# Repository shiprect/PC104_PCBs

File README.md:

# PC104_PCBs
This repository contains a collection of PC104 form factor PCB designs used on a variety of projects.

__Branches__

_previous-revision_  :  for the previous iteration of the pcb that was manufactured

_current-revision_   :  the pcb files that we are currently updating/working on

_production_         : for the version we have currently ordered/produced/are testing

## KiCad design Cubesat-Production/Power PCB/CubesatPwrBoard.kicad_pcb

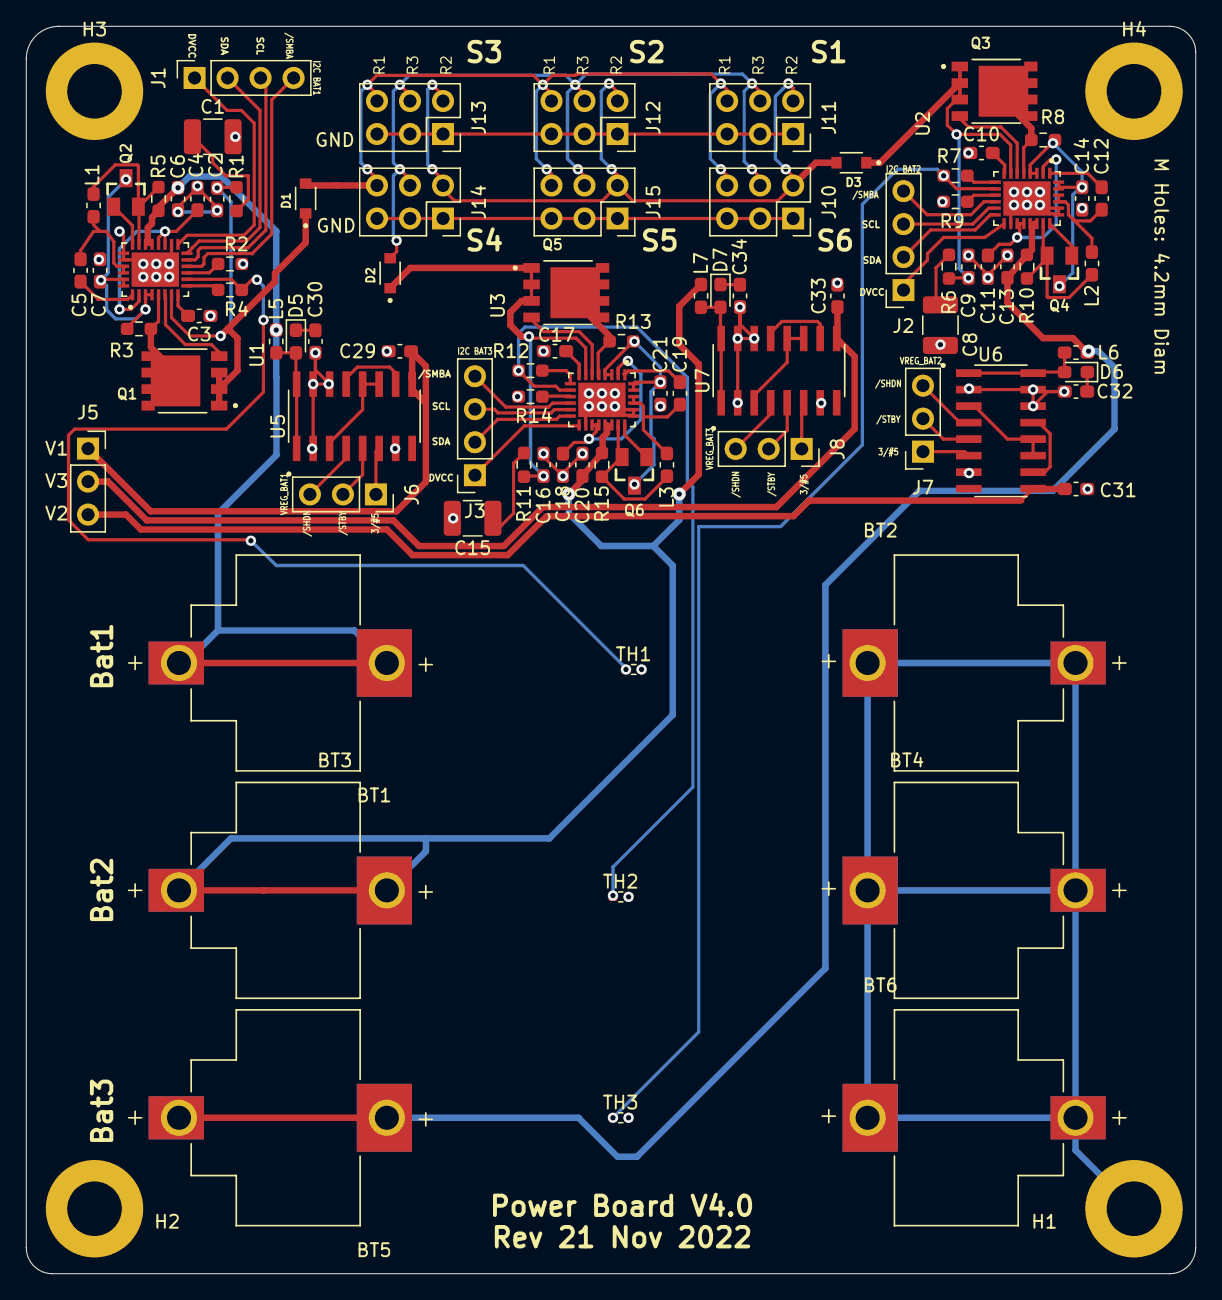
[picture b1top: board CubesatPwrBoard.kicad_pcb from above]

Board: 2 copper layers, 90.0 x 96.0 mm, 92 parts (0 on the bottom side), 85 nets.

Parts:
BT1, BT2, BT3, BT4, BT5, BT6: 254TR; BAT_254TR
C1: C_Polarized_US; C_1210_3225Metric_Pad1.33x2.70mm_HandSolder
C2, C9, C16, C29, C30: C_Polarized_US; C_0603_1608Metric_Pad1.08x0.95mm_HandSolder
C3, C4, C5, C6, C7, C12, C19: C; C_0603_1608Metric_Pad1.08x0.95mm_HandSolder
C8, C15: 150u; C_1210_3225Metric_Pad1.33x2.70mm_HandSolder
C10, C17: 1u; C_0603_1608Metric_Pad1.08x0.95mm_HandSolder
C11, C18, C31, C33: 4.7u; C_0603_1608Metric_Pad1.08x0.95mm_HandSolder
C13, C14, C20, C21: 10u; C_0603_1608Metric_Pad1.08x0.95mm_HandSolder
C32, C34: 100u; C_0603_1608Metric_Pad1.08x0.95mm_HandSolder
D1, D2, D3: D_Schottky_Small; DIO_CUS520,H3F
D5, D6, D7: D_Schottky; D_0603_1608Metric_Pad1.05x0.95mm_HandSolder
H1, H2, H3, H4: MountingHole_Pad; MountingHole_4.3mm_M4_DIN965_Pad
J1, J2, J3: Conn_01x04_Female; PinSocket_1x04_P2.54mm_Vertical
J5: Conn_01x04_Female; PinSocket_1x03_P2.54mm_Vertical
J6, J7, J8: Conn_01x03_Female; PinSocket_1x03_P2.54mm_Vertical
J10: S1; PinSocket_2x03_P2.54mm_Vertical
J11: S2; PinSocket_2x03_P2.54mm_Vertical
J12: S3; PinSocket_2x03_P2.54mm_Vertical
J13: S4; PinSocket_2x03_P2.54mm_Vertical
J14: S5; PinSocket_2x03_P2.54mm_Vertical
J15: S6; PinSocket_2x03_P2.54mm_Vertical
L1, L5: L; L_0603_1608Metric_Pad1.05x0.95mm_HandSolder
L2, L3: 4.7u; L_0603_1608Metric_Pad1.05x0.95mm_HandSolder
L6, L7: 22u; L_0603_1608Metric_Pad1.05x0.95mm_HandSolder
Q1, Q3, Q5: TQM110NB04CR_RLG; TRANS_TQM110NB04CR_RLG
Q2, Q4, Q6: 2N7002*; SOT23
R1, R2, R3, R4, R5: R; R_0603_1608Metric_Pad0.98x0.95mm_HandSolder
R6, R11: 2.5; R_0603_1608Metric_Pad0.98x0.95mm_HandSolder
R7, R8, R12, R13: 16m; R_0603_1608Metric_Pad0.98x0.95mm_HandSolder
R9, R14: 63.4k; R_0603_1608Metric_Pad0.98x0.95mm_HandSolder
R10, R15: 10m; R_0603_1608Metric_Pad0.98x0.95mm_HandSolder
TH1, TH2, TH3: Thermistor_NTC; R_0402_1005Metric_Pad0.72x0.64mm_HandSolder
U1, U2, U3: LTC4162; QFN50P500X400X80-29N
U5, U6, U7: MAX710ESE+T; SOIC127P600X175-16N

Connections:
/Bat_Reg_1/DVCC: J1.1, U1.15 (DVCC)
/Bat_Reg_1/SCL: J1.3, U1.13 (SCL)
/Bat_Reg_1/SDA: J1.2, U1.14 (SDA)
/Bat_Reg_1/TH: R2.2, TH1.1, U1.10 (NTC)
/Bat_Reg_1/VIN: C2.1, D1.1 (K), Q1.1, Q1.2, Q1.3, R1.1, U1.7 (VIN)
/Bat_Reg_1/V_Bat: BT1.P1_1, BT1.P1_2, C6.1, L5.1, R5.1, U1.19 (BATSENS+), U1.20 (CSN)
/Bat_Reg_1//SMBALERT: J1.4, U1.12 (/SMBALERT)
/Bat_Reg_2/DVCC: J3.1, U3.15 (DVCC)
/Bat_Reg_2/SCL: J3.3, U3.13 (SCL)
/Bat_Reg_2/SDA: J3.2, U3.14 (SDA)
/Bat_Reg_2/TH: R12.2, TH2.1, U3.10 (NTC)
/Bat_Reg_2/VIN: C16.1, D2.1 (K), Q5.1, Q5.2, Q5.3, R11.1, U3.7 (VIN)
/Bat_Reg_2/V_Bat: BT3.P1_1, BT3.P1_2, C20.1, L7.1, R15.1, U3.19 (BATSENS+), U3.20 (CSN)
/Bat_Reg_2//SMBALERT: J3.4, U3.12 (/SMBALERT)
/Bat_Reg_3/DVCC: J2.1, U2.15 (DVCC)
/Bat_Reg_3/SCL: J2.3, U2.13 (SCL)
/Bat_Reg_3/SDA: J2.2, U2.14 (SDA)
/Bat_Reg_3/TH: R7.2, TH3.1, U2.10 (NTC)
/Bat_Reg_3/VIN: C9.1, D3.1 (K), Q3.1, Q3.2, Q3.3, R6.1, U2.7 (VIN)
/Bat_Reg_3/V_Bat: BT5.P1_1, BT5.P1_2, C13.1, L6.1, R10.1, U2.19 (BATSENS+), U2.20 (CSN)
/Bat_Reg_3//SMBALERT: J2.4, U2.12 (/SMBALERT)
/V_Reg_3.3_5V1/3/#5: J6.1, U5.6 (3/~5)
/V_Reg_3.3_5V1/#SHDN: J6.3, U5.4 (~SHDN)
/V_Reg_3.3_5V1/#STBY: J6.2, U5.5 (~STBY)
/V_Reg_3.3_5V1/Vout: C29.1, J5.1, U5.9 (OUT)
/V_Reg_3.3_5V2/3/#5: J8.1, U7.6 (3/~5)
/V_Reg_3.3_5V2/#SHDN: J8.3, U7.4 (~SHDN)
/V_Reg_3.3_5V2/#STBY: J8.2, U7.5 (~STBY)
/V_Reg_3.3_5V2/Vout: C33.1, J5.2, U7.9 (OUT)
/V_Reg_3.3_5V3/3/#5: J7.1, U6.6 (3/~5)
/V_Reg_3.3_5V3/#SHDN: J7.3, U6.4 (~SHDN)
/V_Reg_3.3_5V3/#STBY: J7.2, U6.5 (~STBY)
/V_Reg_3.3_5V3/Vout: C31.1, J5.3, U6.9 (OUT)
GND: BT2.P1_1, BT2.P1_2, BT4.P1_1, BT4.P1_2, BT6.P1_1, BT6.P1_2, C1.2, C2.2, C3.1, C4.2, C6.2, C7.2, C8.2, C9.2, C10.1, C11.2, C13.2, C14.2, C15.2, C16.2, C17.1, C18.2, C20.2, C21.2, C29.2, C30.2, C31.2, C32.2, C33.2, C34.2, H1.1, H2.1, H3.1, H4.1, J10.1, J10.3, J10.5, J11.1, J11.3, J11.5, J12.1, J12.3, J12.5, J13.1, J13.3, J13.5, J14.1, J14.3, J14.5, J15.1, J15.3, J15.5, R4.1, R9.1, R14.1, TH1.2, TH2.2, TH3.2, U1.16 (SYNC), U1.23 (PGND), U1.24 (PGND), U1.29 (AGND), U2.16 (SYNC), U2.23 (PGND), U2.24 (PGND), U2.29 (AGND), U3.16 (SYNC), U3.23 (PGND), U3.24 (PGND), U3.29 (AGND), U5.2 (PGND), U5.7 (N/~E), U5.14 (GND), U5.15 (PGND), U6.2 (PGND), U6.7 (N/~E), U6.14 (GND), U6.15 (PGND), U7.2 (PGND), U7.7 (N/~E), U7.14 (GND), U7.15 (PGND)
unnamed: C1.1, R1.2
unnamed: C3.2, U1.8 (VCC2P5)
unnamed: C4.1, U1.2 (INTVCC), U1.17 (CELLS0), U1.18 (CELLS1)
unnamed: C5.1, U1.1 (BOOST)
unnamed: C5.2, L1.1, U1.25 (SW), U1.26 (SW)
unnamed: C7.1, Q2.3, R3.1, U1.3 (VOUTA), U1.4 (CLN), U1.27 (VOUT), U1.28 (VOUT)
unnamed: C8.1, R6.2
unnamed: C10.2, U2.8 (VCC2P5)
unnamed: C11.1, U2.2 (INTVCC), U2.17 (CELLS0), U2.18 (CELLS1)
unnamed: C12.1, U2.1 (BOOST)
unnamed: C12.2, L2.1, U2.25 (SW), U2.26 (SW)
unnamed: C14.1, Q4.3, R8.1, U2.3 (VOUTA), U2.4 (CLN), U2.27 (VOUT), U2.28 (VOUT)
unnamed: C15.1, R11.2
unnamed: C17.2, U3.8 (VCC2P5)
unnamed: C18.1, U3.2 (INTVCC), U3.17 (CELLS0), U3.18 (CELLS1)
unnamed: C19.1, U3.1 (BOOST)
unnamed: C19.2, L3.1, U3.25 (SW), U3.26 (SW)
unnamed: C21.1, Q6.3, R13.1, U3.3 (VOUTA), U3.4 (CLN), U3.27 (VOUT), U3.28 (VOUT)
unnamed: C30.1, D5.1 (K)
unnamed: C32.1, D6.1 (K)
unnamed: C34.1, D7.1 (K)
unnamed: D1.2 (A), J10.6, J11.6, J12.6, J13.6, J14.6, J15.6
unnamed: D2.2 (A), J10.4, J11.4, J12.4, J13.4, J14.4, J15.4
unnamed: D3.2 (A), J10.2, J11.2, J12.2, J13.2, J14.2, J15.2
unnamed: D5.2 (A), L5.2, U5.1 (LX), U5.16 (LX)
unnamed: D6.2 (A), L6.2, U6.1 (LX), U6.16 (LX)
unnamed: D7.2 (A), L7.2, U7.1 (LX), U7.16 (LX)
unnamed: L1.2, Q2.2, R5.2, U1.21 (CSP)
unnamed: L2.2, Q4.2, R10.2, U2.21 (CSP)
unnamed: L3.2, Q6.2, R15.2, U3.21 (CSP)
unnamed: Q1.4, U1.6 (INFET)
unnamed: Q1.5_8, R3.2, U1.5 (CLP)
unnamed: Q2.1, U1.22 (BATFET)
unnamed: Q3.4, U2.6 (INFET)
unnamed: Q3.5_8, R8.2, U2.5 (CLP)
unnamed: Q4.1, U2.22 (BATFET)
unnamed: Q5.4, U3.6 (INFET)
unnamed: Q5.5_8, R13.2, U3.5 (CLP)
unnamed: Q6.1, U3.22 (BATFET)
unnamed: R2.1, U1.9 (NTCBIAS)
unnamed: R4.2, U1.11 (RT)
unnamed: R7.1, U2.9 (NTCBIAS)
unnamed: R9.2, U2.11 (RT)
unnamed: R12.1, U3.9 (NTCBIAS)
unnamed: R14.2, U3.11 (RT)
unnamed: U5.10 (LBI-), U5.13 (REF)
unnamed: U5.3 (ILIM), U5.11 (LBI+), U5.12 (PS)
unnamed: U6.10 (LBI-), U6.13 (REF)
unnamed: U6.3 (ILIM), U6.11 (LBI+), U6.12 (PS)
unnamed: U7.10 (LBI-), U7.13 (REF)
unnamed: U7.3 (ILIM), U7.11 (LBI+), U7.12 (PS)

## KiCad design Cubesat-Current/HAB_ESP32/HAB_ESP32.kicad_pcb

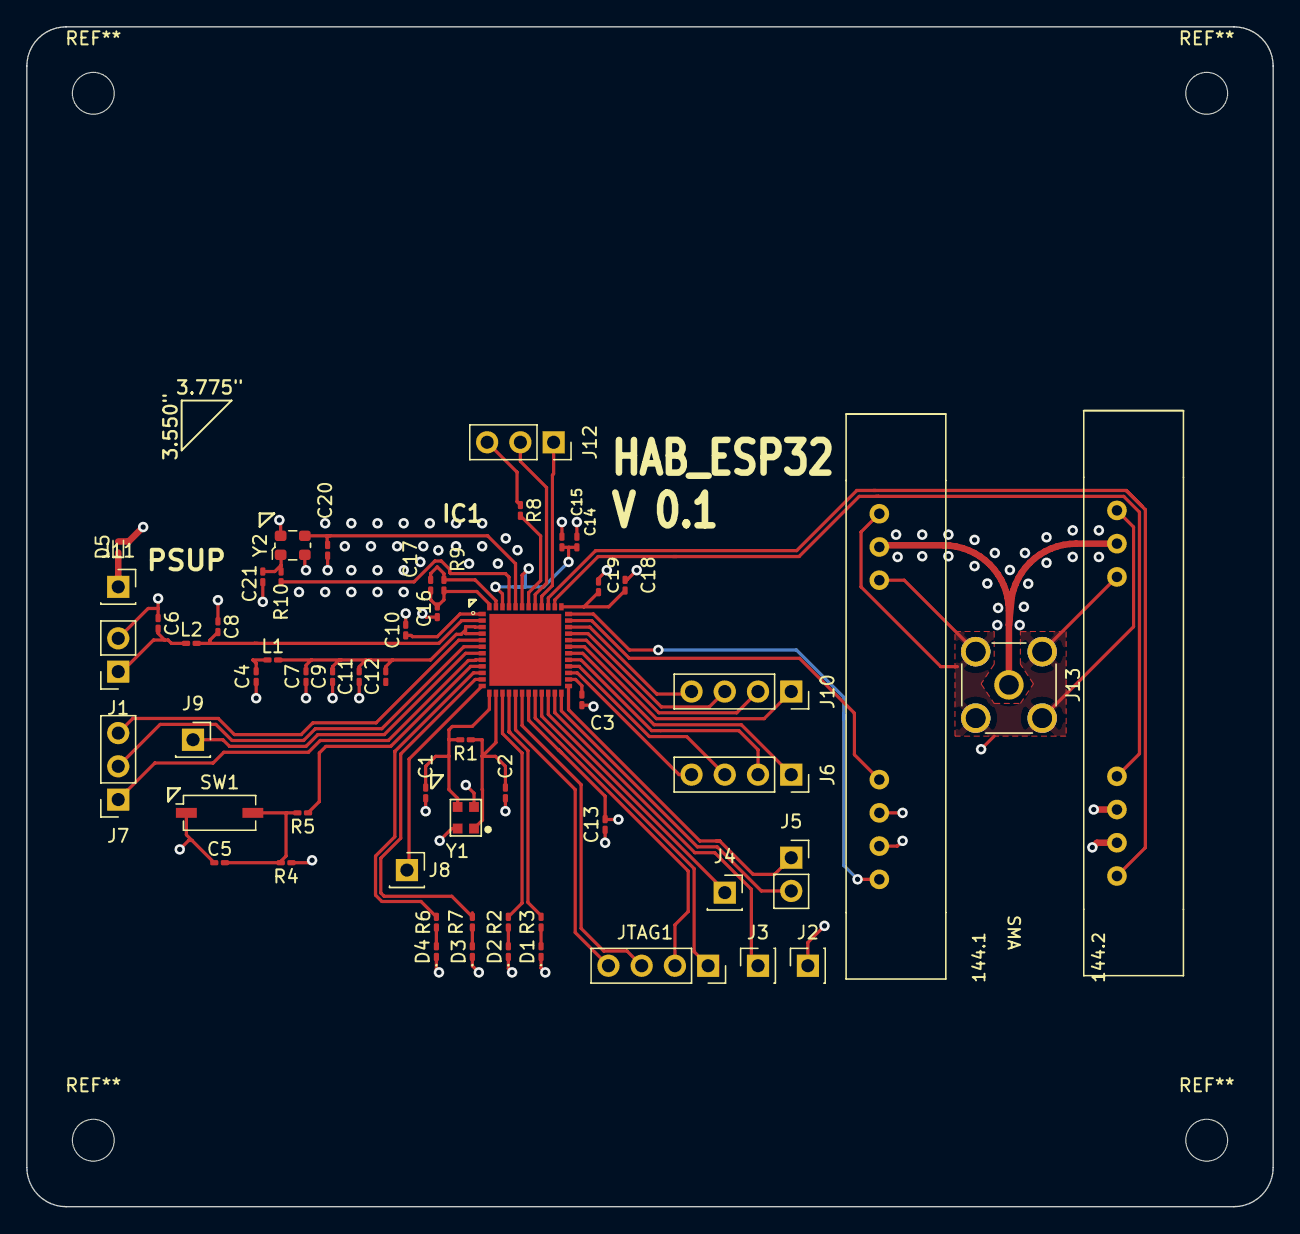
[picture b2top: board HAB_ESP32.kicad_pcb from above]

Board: 4 copper layers, 95.2 x 90.2 mm, 58 parts (0 on the bottom side), 54 nets.

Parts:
144.1, 144.2: Radiometic_HX1; Radiometric_HX1
C1, C2, C6, C8, C20: TBD; C_0201_0603Metric_Pad0.64x0.40mm_HandSolder
C3, C5, C9, C15, C19: 1u; C_0201_0603Metric_Pad0.64x0.40mm_HandSolder
C4, C11, C16, C21: C; C_0201_0603Metric_Pad0.64x0.40mm_HandSolder
C7, C10, C13: 0.1u; C_0201_0603Metric_Pad0.64x0.40mm_HandSolder
C12, C18: 10u; C_0201_0603Metric_Pad0.64x0.40mm_HandSolder
C14: 100p; C_0201_0603Metric_Pad0.64x0.40mm_HandSolder
C17: 3.3n; C_0201_0603Metric_Pad0.64x0.40mm_HandSolder
D1, D2, D3, D4: LED; LED_0201_0603Metric_Pad0.64x0.40mm_HandSolder
D5: ESD9B3.3ST5G; D_SOD-923
IC1: ESP32-PICO-D4; ESP32-PICO-D4_1
J1, J5: PinSocket_1x02_P2.54mm_Vertical
J2, J3, J4, J8, J9, J11: PinSocket_1x01_P2.54mm_Vertical
J6, J10: PinSocket_1x04_P2.54mm_Vertical
J7, J12: PinSocket_1x03_P2.54mm_Vertical
J13: SMA_Molex_Horizontal; SMA_Molex_73251-2200_Horizontal
JTAG1: PinSocket_1x04_P2.54mm_Vertical
L1: 2n; L_0201_0603Metric_Pad0.64x0.40mm_HandSolder
L2: TBD; L_0201_0603Metric_Pad0.64x0.40mm_HandSolder
R1, R2, R3, R4, R6, R7: TBD; R_0201_0603Metric_Pad0.64x0.40mm_HandSolder
R5, R10: 0; R_0201_0603Metric_Pad0.64x0.40mm_HandSolder
R8: 499; R_0201_0603Metric_Pad0.64x0.40mm_HandSolder
R9: 20k; R_0201_0603Metric_Pad0.64x0.40mm_HandSolder
SW1: SW_SPST; SW_DIP_SPSTx01_Slide_Copal_CHS-01A_W5.08mm_P1.27mm_JPin
Y1: OM-7604-C7; OSCDFN250X200X89-4N
Y2: ECS-TXO-2520-33-400-AN-TR; Oscillator_SMD_ECS_2520MV-xxx-xx-4Pin_2.5x2.0mm

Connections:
/ANT: C6.2, J1.1, L2.1
/CLK-SCK1: IC1.31, J10.1
/IO0: IC1.23, J3.1
/IO2: IC1.22, J4.1
/IO4: IC1.24, J5.2
/IO5: IC1.34, J10.4
/IO12: IC1.18, JTAG1.3
/IO13: IC1.20, JTAG1.2
/IO14: IC1.17, JTAG1.4
/IO15: IC1.21, JTAG1.1
/IO16: IC1.25, J5.1
/IO17: IC1.27, J6.4
/IO18: 144.1.4, IC1.35
/IO19: 144.2.4, IC1.38
/IO21: J12.3, R8.1
/IO22: 144.2.7, IC1.39
/IO23: 144.1.7, IC1.36
/IO26: IC1.15, R2.2
/IO27: IC1.16, R3.2
/IO32: IC1.12, J8.1
/IO34: IC1.10, R6.1
/IO35: IC1.11, R7.1
/Psup: D5.1, J11.1
/SCS-CMD: IC1.30, J6.1
/SDI-SD1: IC1.33, J10.3
/SDO-SD0: IC1.32, J10.2
/SHD-SD2: IC1.28, J6.3
/SWP-SD3: IC1.29, J6.2
/S_CAPN: IC1.7, J9.1
/S_CAPP: IC1.6, J7.2
/S_VN: IC1.8, J7.1
/S_VP: IC1.5, J7.3
/U0TXD: IC1.41, J12.2
/UORXD: IC1.40, J12.1
GND: 144.1.1, 144.1.3, 144.1.6, 144.2.1, 144.2.3, 144.2.6, C1.1, C2.1, C3.1, C4.1, C5.1, C6.1, C7.1, C8.1, C9.1, C10.1, C11.1, C12.1, C13.1, C14.2, C15.2, C16.2, C18.1, C19.1, C20.2, C21.2, D1.1, D2.1, D3.1, D4.1, IC1.49, J1.2, J2.1, J13.2, SW1.1, Y1.2, Y2.2
unnamed: 144.1.2, 144.2.2, J13.1
unnamed: C1.2, IC1.13, R1.2, Y1.3
unnamed: C2.2, IC1.14, R1.1, Y1.1
unnamed: C5.2, R4.2, R5.2, SW1.2
unnamed: C8.2, IC1.2, L2.2
unnamed: C7.2, C9.2, C11.2, C12.2, IC1.3, IC1.4, L1.2
unnamed: C14.1, C15.1, IC1.43, IC1.46
unnamed: C16.1, C17.1, IC1.48, R9.2
unnamed: C17.2, IC1.47, R9.1
unnamed: C20.1, IC1.44, Y2.3
unnamed: C21.1, R10.1, Y2.1
unnamed: D1.2, R3.1
unnamed: D2.2, R2.1
unnamed: D3.2, R7.2
unnamed: D4.2, R6.2
unnamed: IC1.9, R5.1
unnamed: IC1.42, R8.2
unnamed: IC1.45, R10.2
VCC: 144.1.5, 144.2.5, C3.2, C4.2, C10.2, C13.2, C18.2, C19.2, D5.2, IC1.1, IC1.19, IC1.26, IC1.37, L1.1, R4.1, Y1.4, Y2.4

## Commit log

2022-07-24 Current version commit
    committing current versions of power and esp32 to production branch
2022-07-24 name change commit
    changed name from current to production
2022-07-24 initial current version commit
2022-07-24 initial previous version commit
2022-11-22 Major revision to power board, three battery design v1
2022-11-22 Previous version commit
2022-11-22 Major three battery revision version 1
2022-11-22 Pushing previous single battery version to previous branch
2022-11-22 added to silkscreen and exported fabrication files
2022-11-22 Forgot to readd ground plane after making changes
2022-11-22 Fixed footprint size of 150uF caps
2022-12-09 Added mounting holes to paste layer for future stencil fabrication
2022-12-15 Changed mounting holes to 4.2mm diameter and added silkscreen text
2023-03-03 minor changes
2023-03-03 minor changes to board
2023-03-03 copies current-revision to production branch
2023-03-03 Added missing component values
2023-03-31 Added text file with list of changes to make to power board after having tested it
2023-05-03 Small changes to board before moving to previous-revision
2023-05-03 moving prod to prev revision branch
2023-05-03 Major revision V5.0, will add to changelog later
2023-05-03 Updating to revision 5.0
2023-05-03 Final update for version 5, should be ready for shipping out
2023-05-03 Final V5 revision, should be ready for purchase
2023-05-03 rotated one designator
2023-05-03 Rotated one text symboland realigned mounting holes
2023-05-03 rotated one text and realigned mounting holes
2023-05-03 Adjusted some text
2023-05-03 Deleted some unecessary files
2023-05-04 Added gerbers
